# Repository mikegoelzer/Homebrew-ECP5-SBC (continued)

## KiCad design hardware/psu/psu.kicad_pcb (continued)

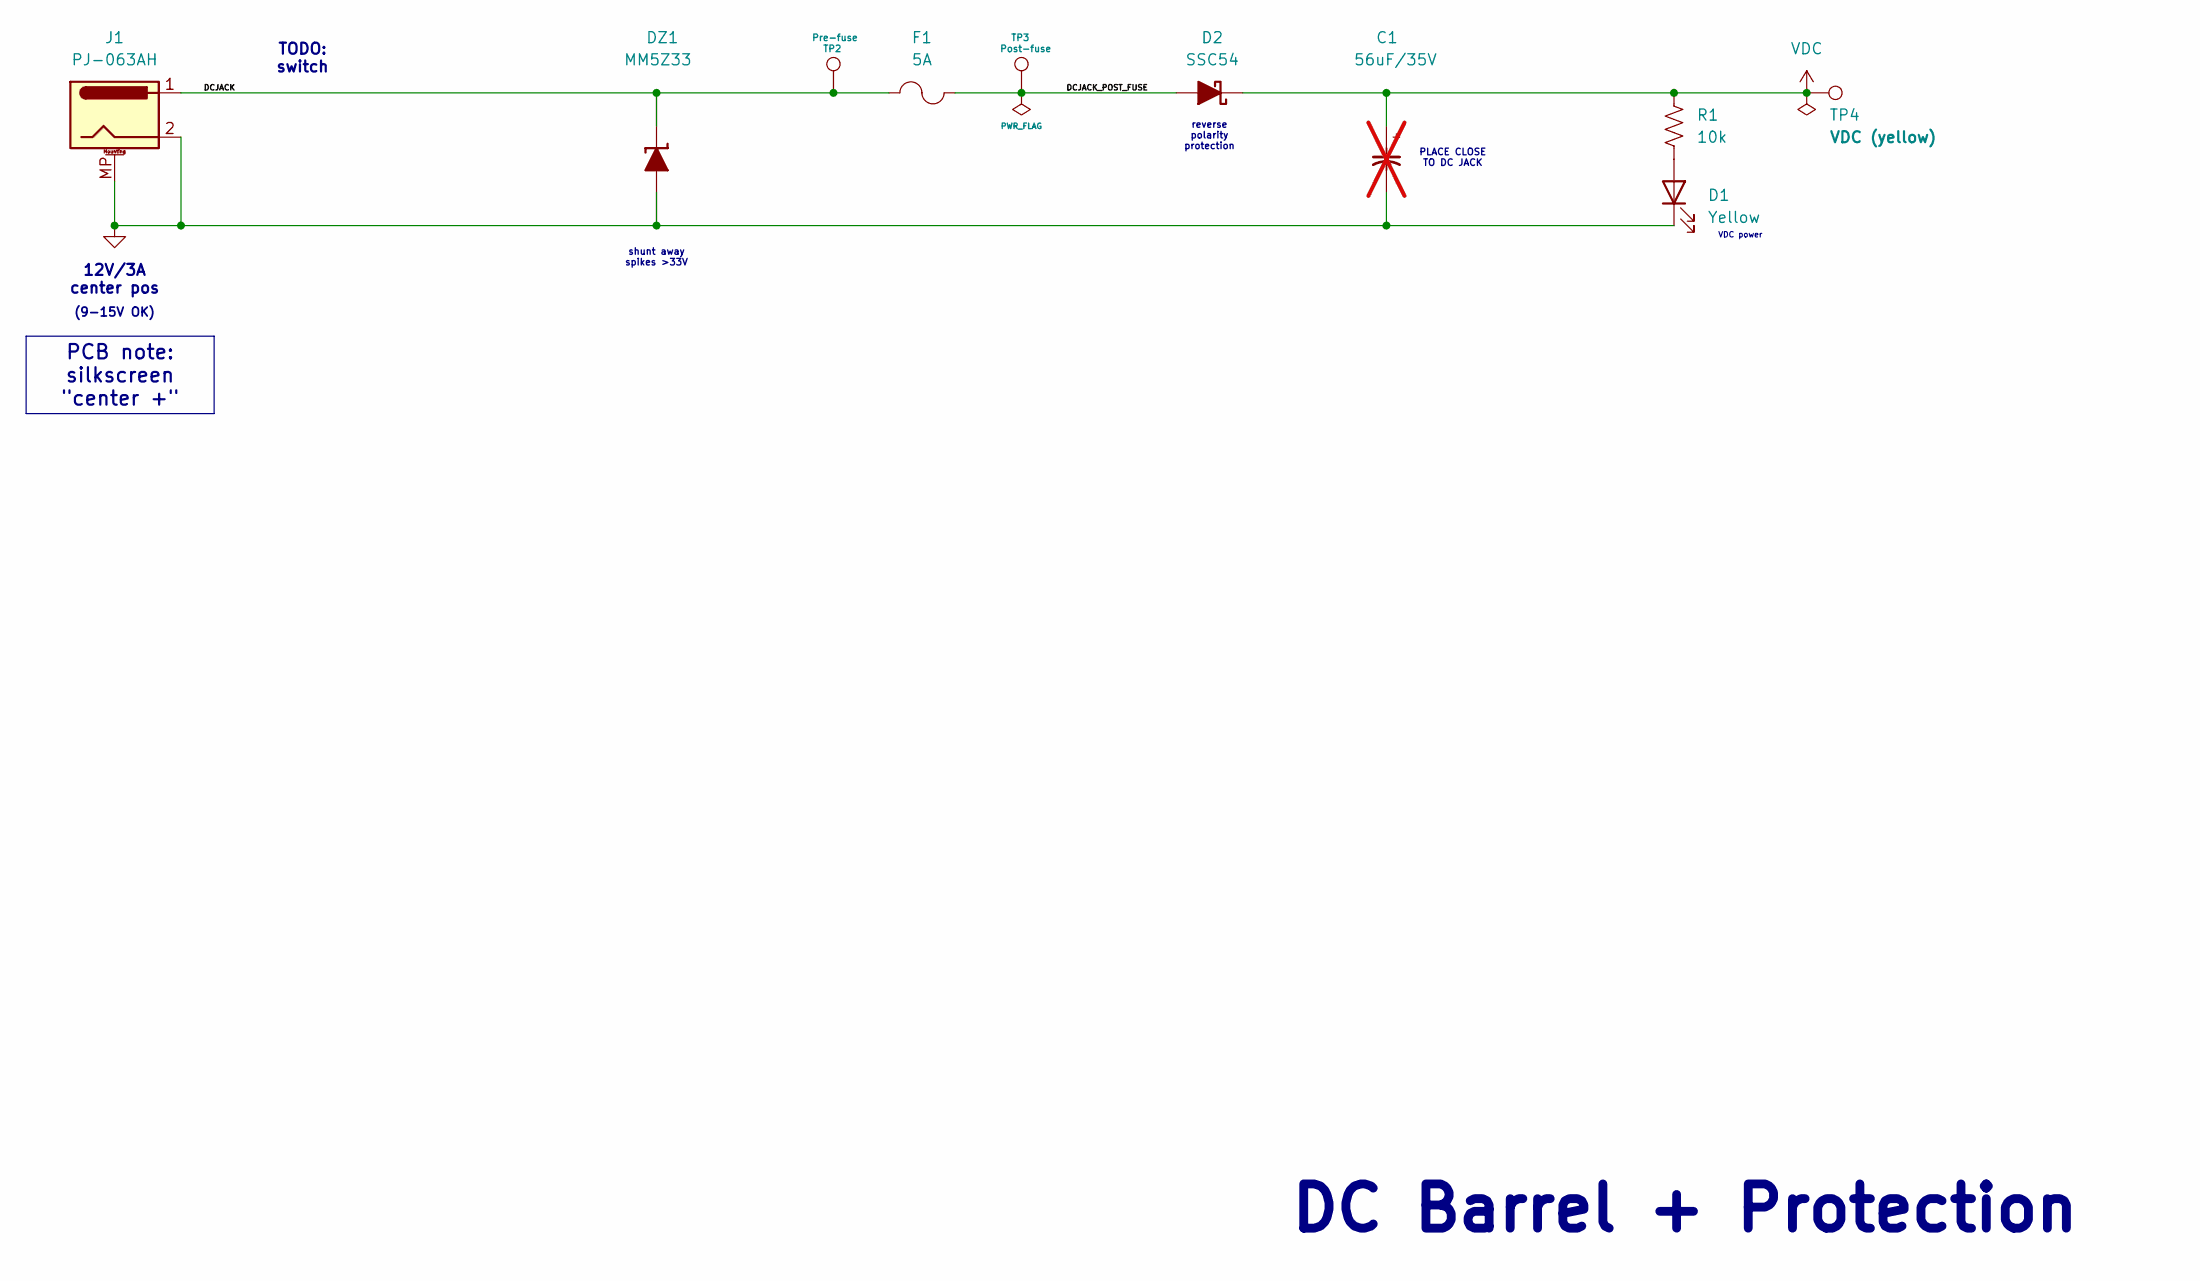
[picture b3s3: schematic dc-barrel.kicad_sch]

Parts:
C1: 56uF/35V; CAP_PC_8X10_NCH; MPN PCV1V560MCL1GS; not fitted
D1: Yellow; LED_0603_1608Metric_Pad1.05x0.95mm_HandSolder; MPN 150060YS75000
D2: SSC54; D_SMC; MPN SSC54-E3/57T
DZ1: MM5Z33; D_SOD-523; MPN MM5Z33VT1G
F1: 5A; Fuseholder_Cylinder-5x20mm_Wuerth_696103101002-SMD_Horizont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; MPN1 696103101002
J1: PJ-063AH; BarrelJack_CUI_PJ-063AH_Horizontal; MPN PJ-063AH
R1: 10k; R_0603_1608Metric_Pad1.05x0.95mm_HandSolder; MPN RC0603FR-0710KL
TP2: Pre-fuse; TestPoint_Pad_2.0x2.0mm
TP3: Post-fuse; TestPoint_Pad_2.0x2.0mm
TP4: VDC (yellow); TestPoint_Keystone_5000-5004_Miniature; MPN 5004

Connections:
/DC Barrel/DCJACK: DZ1.1 (K), F1.1, J1.1, TP2.1
/DC Barrel/DCJACK_POST_FUSE: D2.2 (A), F1.2, TP3.1
GND: C1.2, D1.1 (K), DZ1.2 (A), J1.2, J1.MP (MountPin); also elsewhere on the board
unnamed: D1.2 (A), R1.2
VDC: C1.1, D2.1 (K), R1.1, TP4.1; also elsewhere on the board

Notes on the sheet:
PCB note: silkscreen "center +"
TODO: switch
12V/3A center pos
VDC power
shunt away spikes >33V
DC Barrel + Protection
(9-15V OK)
PLACE CLOSE TO DC JACK
reverse polarity protection

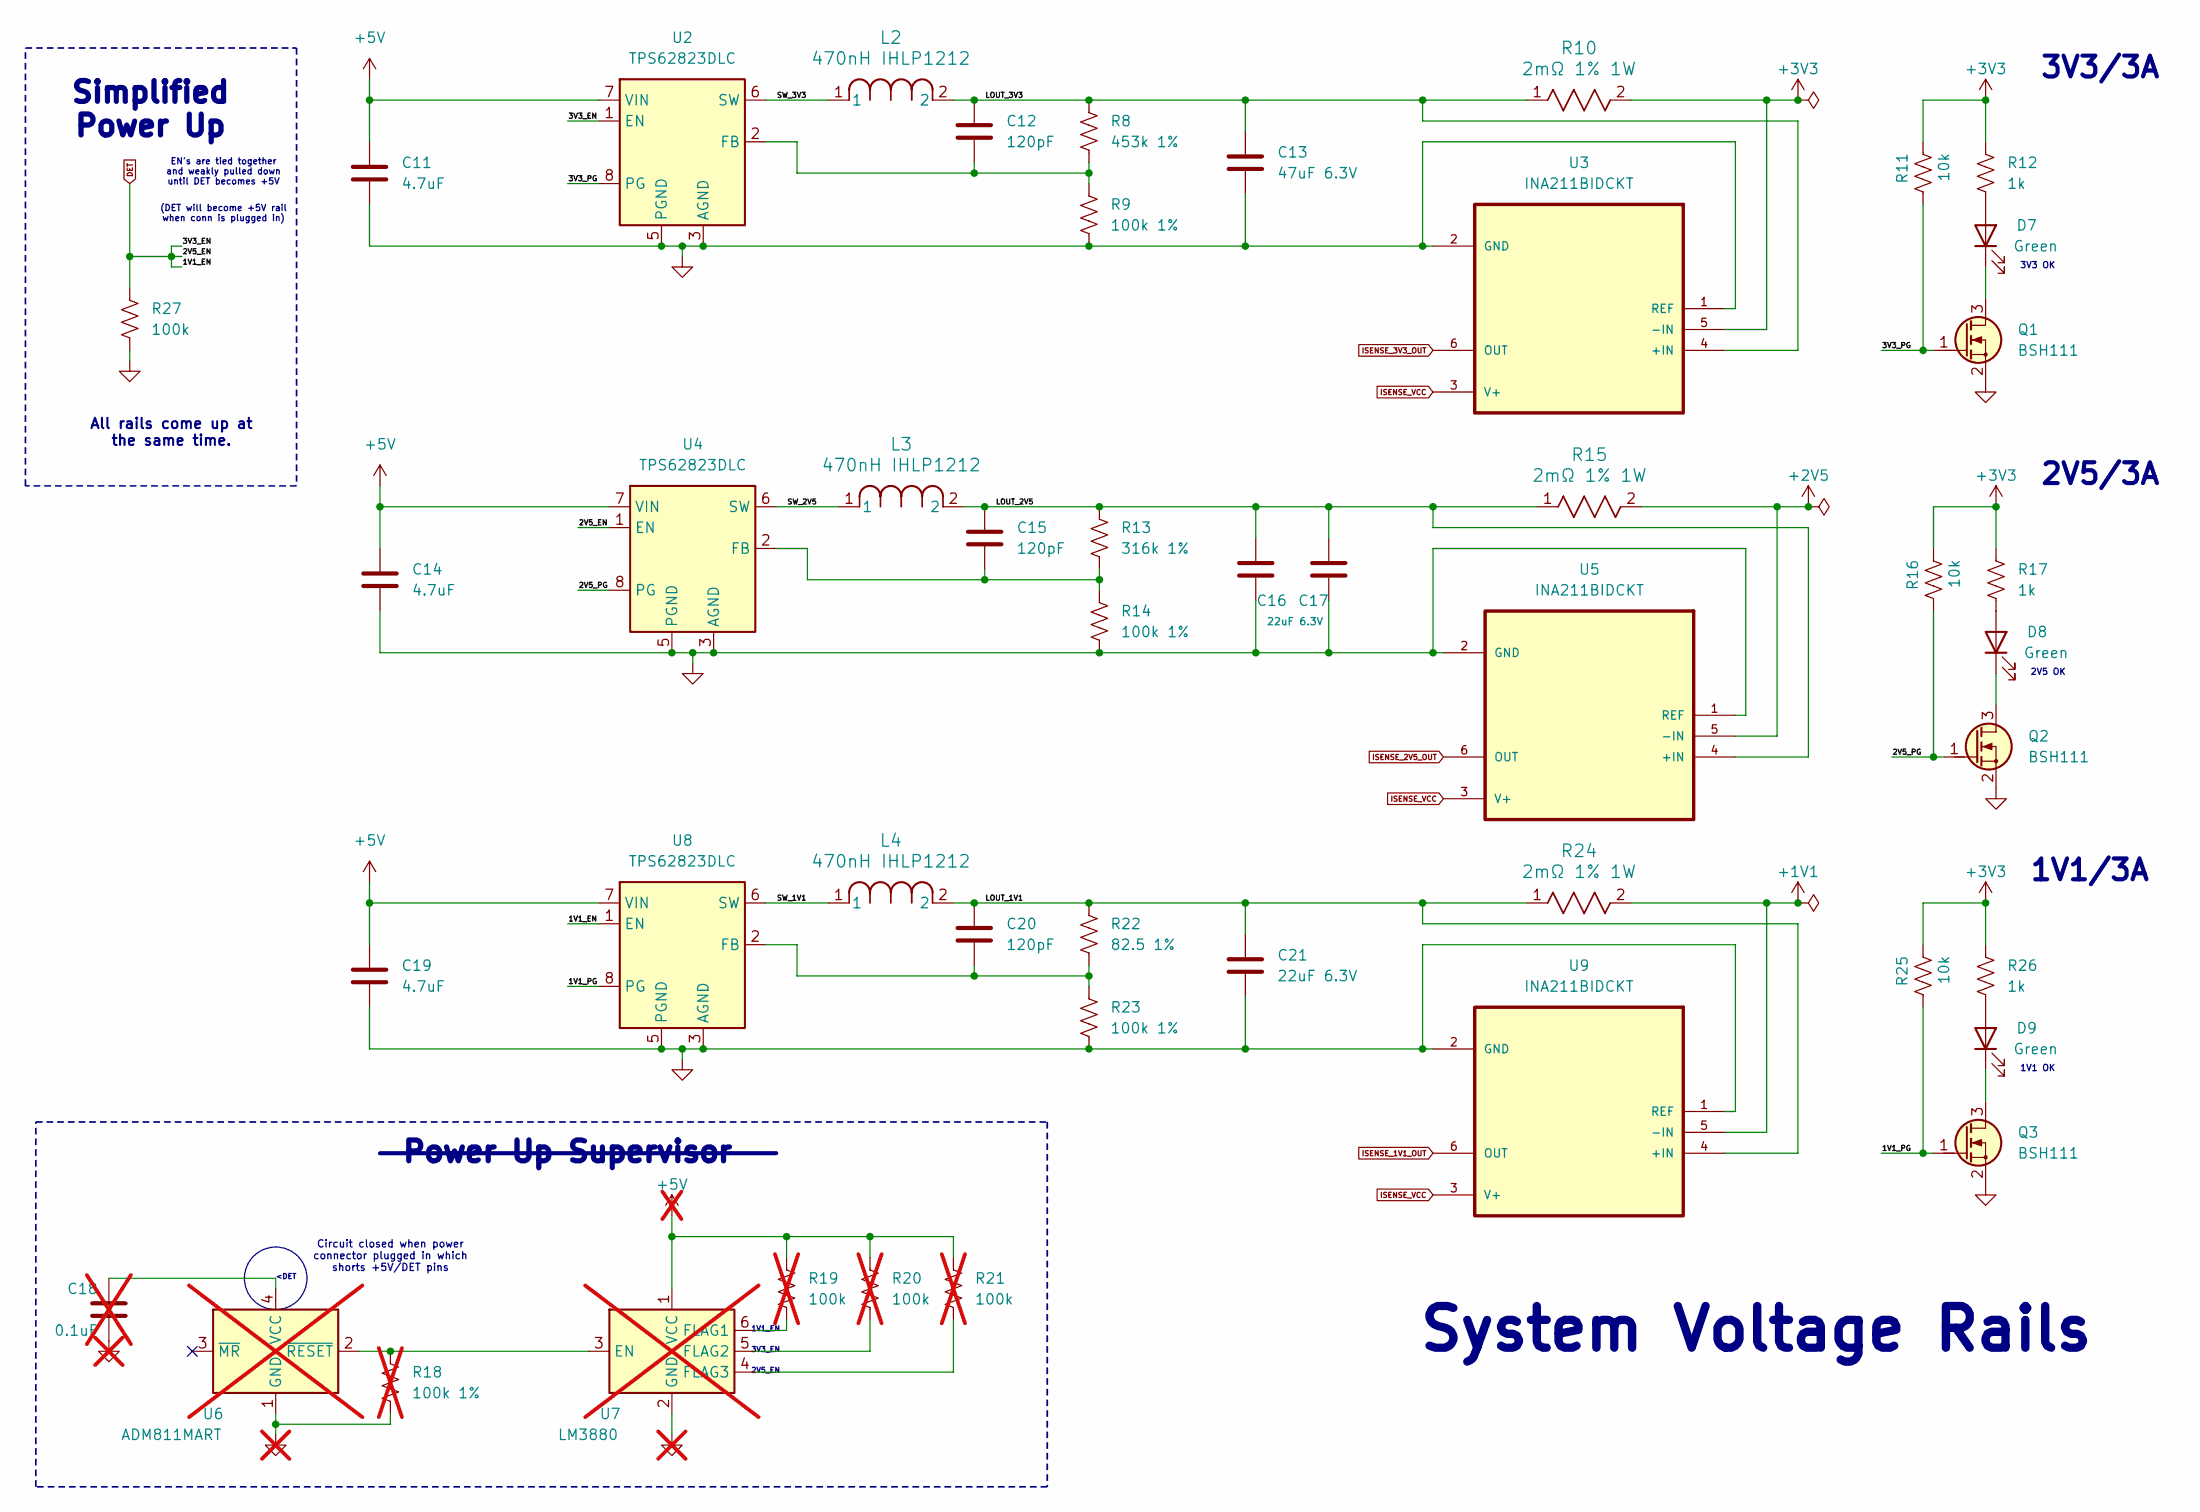
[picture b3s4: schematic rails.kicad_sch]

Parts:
C11, C14, C19: 4.7uF; C_0805_2012Metric_Pad1.18x1.45mm_HandSolder; MPN C0805C475K8PAC7800
C12: 120pF; C_0805_2012Metric_Pad1.18x1.45mm_HandSolder; MPN KGM21BCG1H121JT
C13: 47uF 6.3V; C_1206_3216Metric_Pad1.33x1.80mm_HandSolder; MPN GRM31CR60J476KE19L
C15, C20: 120pF; C_0603_1608Metric_Pad1.08x0.95mm_HandSolder; MPN GRM1885C1H121JA01D
C16, C17, C21: 22uF 6.3V; C_0603_1608Metric_Pad1.08x0.95mm_HandSolder; MPN GRM188R60J226MEA0D
C18: 0.1uF; C_0603_1608Metric_Pad1.08x0.95mm_HandSolder; MPN GRM188R72A104KA35D; not fitted
D7, D8, D9: Green; LED_0603_1608Metric_Pad1.05x0.95mm_HandSolder; MPN 150060VS75000
L2, L3, L4: 470nH IHLP1212; L_Vishay_IHLP-1212; MPN IHLP1212AEERR47M11
Q1, Q2, Q3: BSH111; SOT-23; MPN BSH111BKR
R8: 453k 1%; R_0805_2012Metric_Pad1.15x1.40mm_HandSolder; MPN ERJ-6ENF4533V
R9, R14, R23: 100k 1%; R_0805_2012Metric_Pad1.15x1.40mm_HandSolder; MPN CRCW0805100KFKEA
R10, R15, R24: 2mΩ 1% 1W; STA_CSNL1206_STP; MPN CSNL1206FT2L00
R11, R16, R25: 10k; R_0603_1608Metric_Pad1.05x0.95mm_HandSolder; MPN RC0603FR-0710KL
R12, R17, R26: 1k; R_0603_1608Metric_Pad1.05x0.95mm_HandSolder; MPN RC0603FR-071KL
R13: 316k 1%; R_0805_2012Metric_Pad1.15x1.40mm_HandSolder; MPN ERJ-6ENF3163V
R18: 100k 1%; R_0603_1608Metric_Pad0.98x0.95mm_HandSolder; MPN RC0603FR-07100KL; not fitted
R19, R20, R21: 100k; R_0603_1608Metric_Pad0.98x0.95mm_HandSolder; MPN RC0603FR-07100KL; not fitted
R22: 82.5 1%; R_0805_2012Metric_Pad1.15x1.40mm_HandSolder; MPN ERJ-6ENF8252V
R27: 100k; R_0603_1608Metric_Pad0.98x0.95mm_HandSolder; MPN RC0603FR-07100KL
U2, U4, U8: TPS62823DLC; Texas_VSON-HR-8_1.5x2mm_P0.5mm; MPN TPS62823DLCR
U3, U5, U9: INA211BIDCKT; SOT65P210X110-6N; MPN INA211BIDCKT
U6: ADM811MART; SOT-143; MPN ADM811MARTZ-REEL7; not fitted
U7: LM3880; SOT-23-6; not fitted

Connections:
+1V1: R24.2, U9.5 (-IN); also elsewhere on the board
+2V5: R15.2, U5.5 (-IN); also elsewhere on the board
+3V3: R10.2, R11.2, R12.2, R16.2, R17.2, R25.2, R26.2, U3.5 (-IN); also elsewhere on the board
+5V: C11.1, C14.1, C19.1, R19.1, R20.1, R21.1, U2.7 (VIN), U4.7 (VIN), U7.1 (VCC), U8.7 (VIN); also elsewhere on the board
/Rails/1V1_PG: Q3.1 (G), R25.1, U8.8 (PG)
/Rails/2V5_PG: Q2.1 (G), R16.1, U4.8 (PG)
/Rails/3V3_PG: Q1.1 (G), R11.1, U2.8 (PG)
/Rails/LOUT_1V1: C20.1, C21.1, L4.2, R22.1, R24.1, U9.4 (+IN)
/Rails/LOUT_2V5: C15.1, C16.1, C17.1, L3.2, R13.1, R15.1, U5.4 (+IN)
/Rails/LOUT_3V3: C12.1, C13.1, L2.2, R8.1, R10.1, U3.4 (+IN)
/Rails/SW_1V1: L4.1, U8.6 (SW)
/Rails/SW_2V5: L3.1, U4.6 (SW)
/Rails/SW_3V3: L2.1, U2.6 (SW)
DET: R27.1, U2.1 (EN), U4.1 (EN), U8.1 (EN); also elsewhere on the board
GND: C11.2, C13.2, C14.2, C16.2, C17.2, C18.2, C19.2, C21.2, Q1.2 (S), Q2.2 (S), Q3.2 (S), R9.2, R14.2, R18.2, R23.2, R27.2, U2.3 (AGND), U2.5 (PGND), U3.1 (REF), U3.2 (GND), U4.3 (AGND), U4.5 (PGND), U5.1 (REF), U5.2 (GND), U6.1 (GND), U7.2 (GND), U8.3 (AGND), U8.5 (PGND), U9.1 (REF), U9.2 (GND); also elsewhere on the board
ISENSE_1V1_OUT: U9.6 (OUT); also elsewhere on the board
ISENSE_2V5_OUT: U5.6 (OUT); also elsewhere on the board
ISENSE_3V3_OUT: U3.6 (OUT); also elsewhere on the board
ISENSE_VCC: U3.3 (V+), U5.3 (V+), U9.3 (V+); also elsewhere on the board
unnamed: C18.1, U6.4 (VCC)
unnamed: D7.2 (A), R12.1
unnamed: D7.1 (K), Q1.3 (D)
unnamed: D8.2 (A), R17.1
unnamed: D8.1 (K), Q2.3 (D)
unnamed: D9.2 (A), R26.1
unnamed: D9.1 (K), Q3.3 (D)
unnamed: R18.1, U6.2 (~RESET), U7.3 (EN)
unnamed: R19.2, U7.6 (FLAG1)
unnamed: R20.2, U7.5 (FLAG2)
unnamed: R21.2, U7.4 (FLAG3)
unnamed: C12.2, R8.2, R9.1, U2.2 (FB)
unnamed: C15.2, R13.2, R14.1, U4.2 (FB)
unnamed: C20.2, R22.2, R23.1, U8.2 (FB)

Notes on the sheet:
2V5/3A
Simplified Power Up
3V3_EN
3V3 OK
(DET will become +5V rail when conn is plugged in)
3V3/3A
<DET
System Voltage Rails
1V1_EN
2V5_EN
All rails come up at the same time.
Power Up Supervisor
Circuit closed when power connector plugged in which shorts +5V/DET pins
2V5 OK
EN's are tied together and weakly pulled down until DET becomes +5V
1V1 OK
1V1/3A

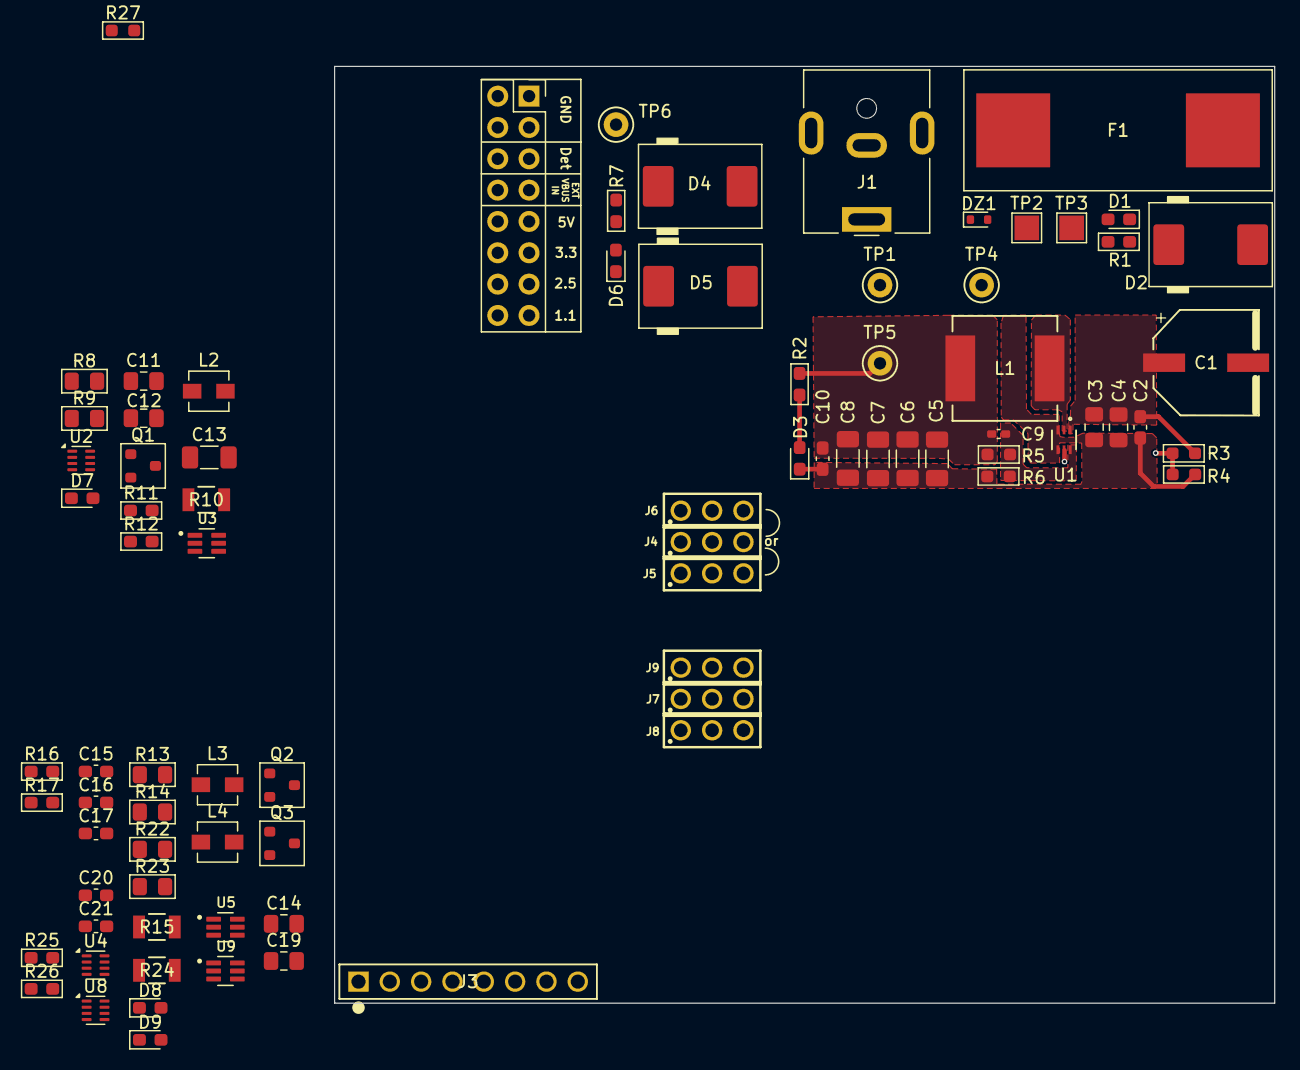
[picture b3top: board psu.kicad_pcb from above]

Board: 4 copper layers, 76.2 x 75.9 mm, 83 parts (0 on the bottom side), 41 nets.

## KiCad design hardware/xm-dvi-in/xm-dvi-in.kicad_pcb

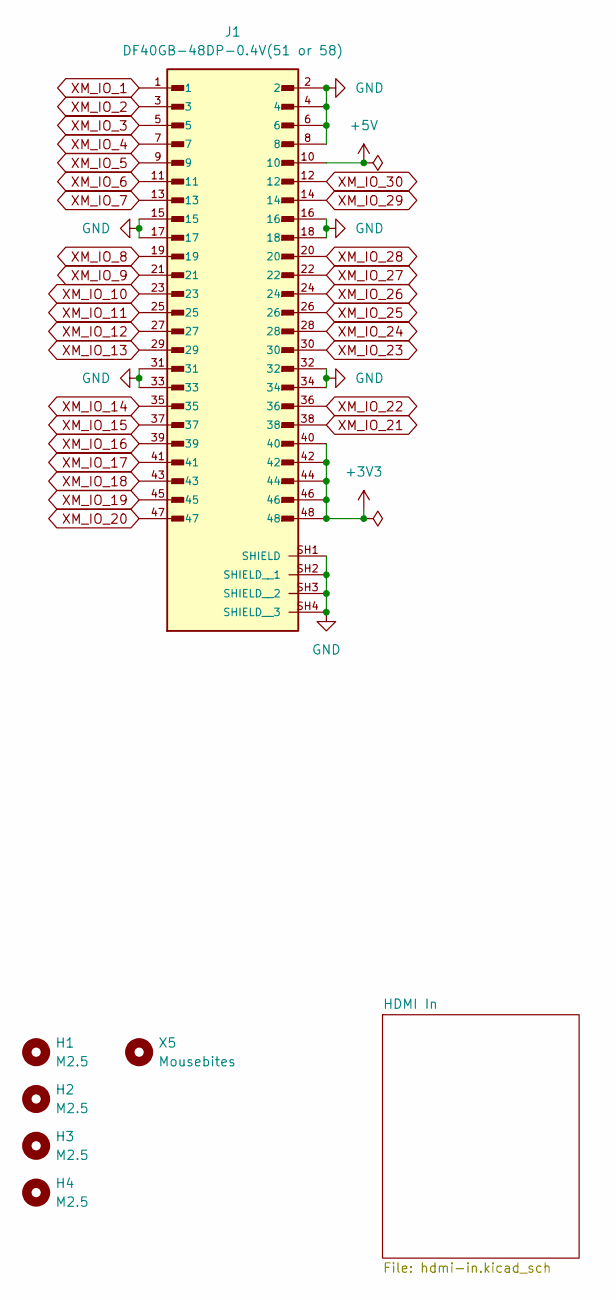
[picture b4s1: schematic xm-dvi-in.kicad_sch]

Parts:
H1, H2, H3, H4: M2.5; MountingHole_2.7mm_M2.5
J1: DF40GB-48DP-0.4V(51 or 58); HIROSE_DF40GB-48DP-0.4V_58_; MPN DF40GB-48DP-0.4V(51)
X5: Mousebites; mouse-bite-2.54mm-slot

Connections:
+3V3: J1.40, J1.42, J1.44, J1.46, J1.48; also elsewhere on the board
+5V: J1.10; also elsewhere on the board
GND: J1.2, J1.4, J1.6, J1.8, J1.15, J1.16, J1.17, J1.18, J1.31, J1.32, J1.33, J1.34, J1.SH1 (SHIELD), J1.SH2 (SHIELD__1), J1.SH3 (SHIELD__2), J1.SH4 (SHIELD__3); also elsewhere on the board
XM_IO_1: J1.1
XM_IO_2: J1.3
XM_IO_3: J1.5
XM_IO_4: J1.7
XM_IO_5: J1.9
XM_IO_6: J1.11
XM_IO_7: J1.13
XM_IO_8: J1.19
XM_IO_9: J1.21
XM_IO_10: J1.23
XM_IO_11: J1.25
XM_IO_12: J1.27
XM_IO_13: J1.29
XM_IO_14: J1.35
XM_IO_15: J1.37
XM_IO_16: J1.39
XM_IO_17: J1.41
XM_IO_18: J1.43
XM_IO_19: J1.45
XM_IO_20: J1.47
XM_IO_21: J1.38
XM_IO_22: J1.36
XM_IO_23: J1.30
XM_IO_24: J1.28
XM_IO_25: J1.26
XM_IO_26: J1.24
XM_IO_27: J1.22
XM_IO_28: J1.20
XM_IO_29: J1.14
XM_IO_30: J1.12

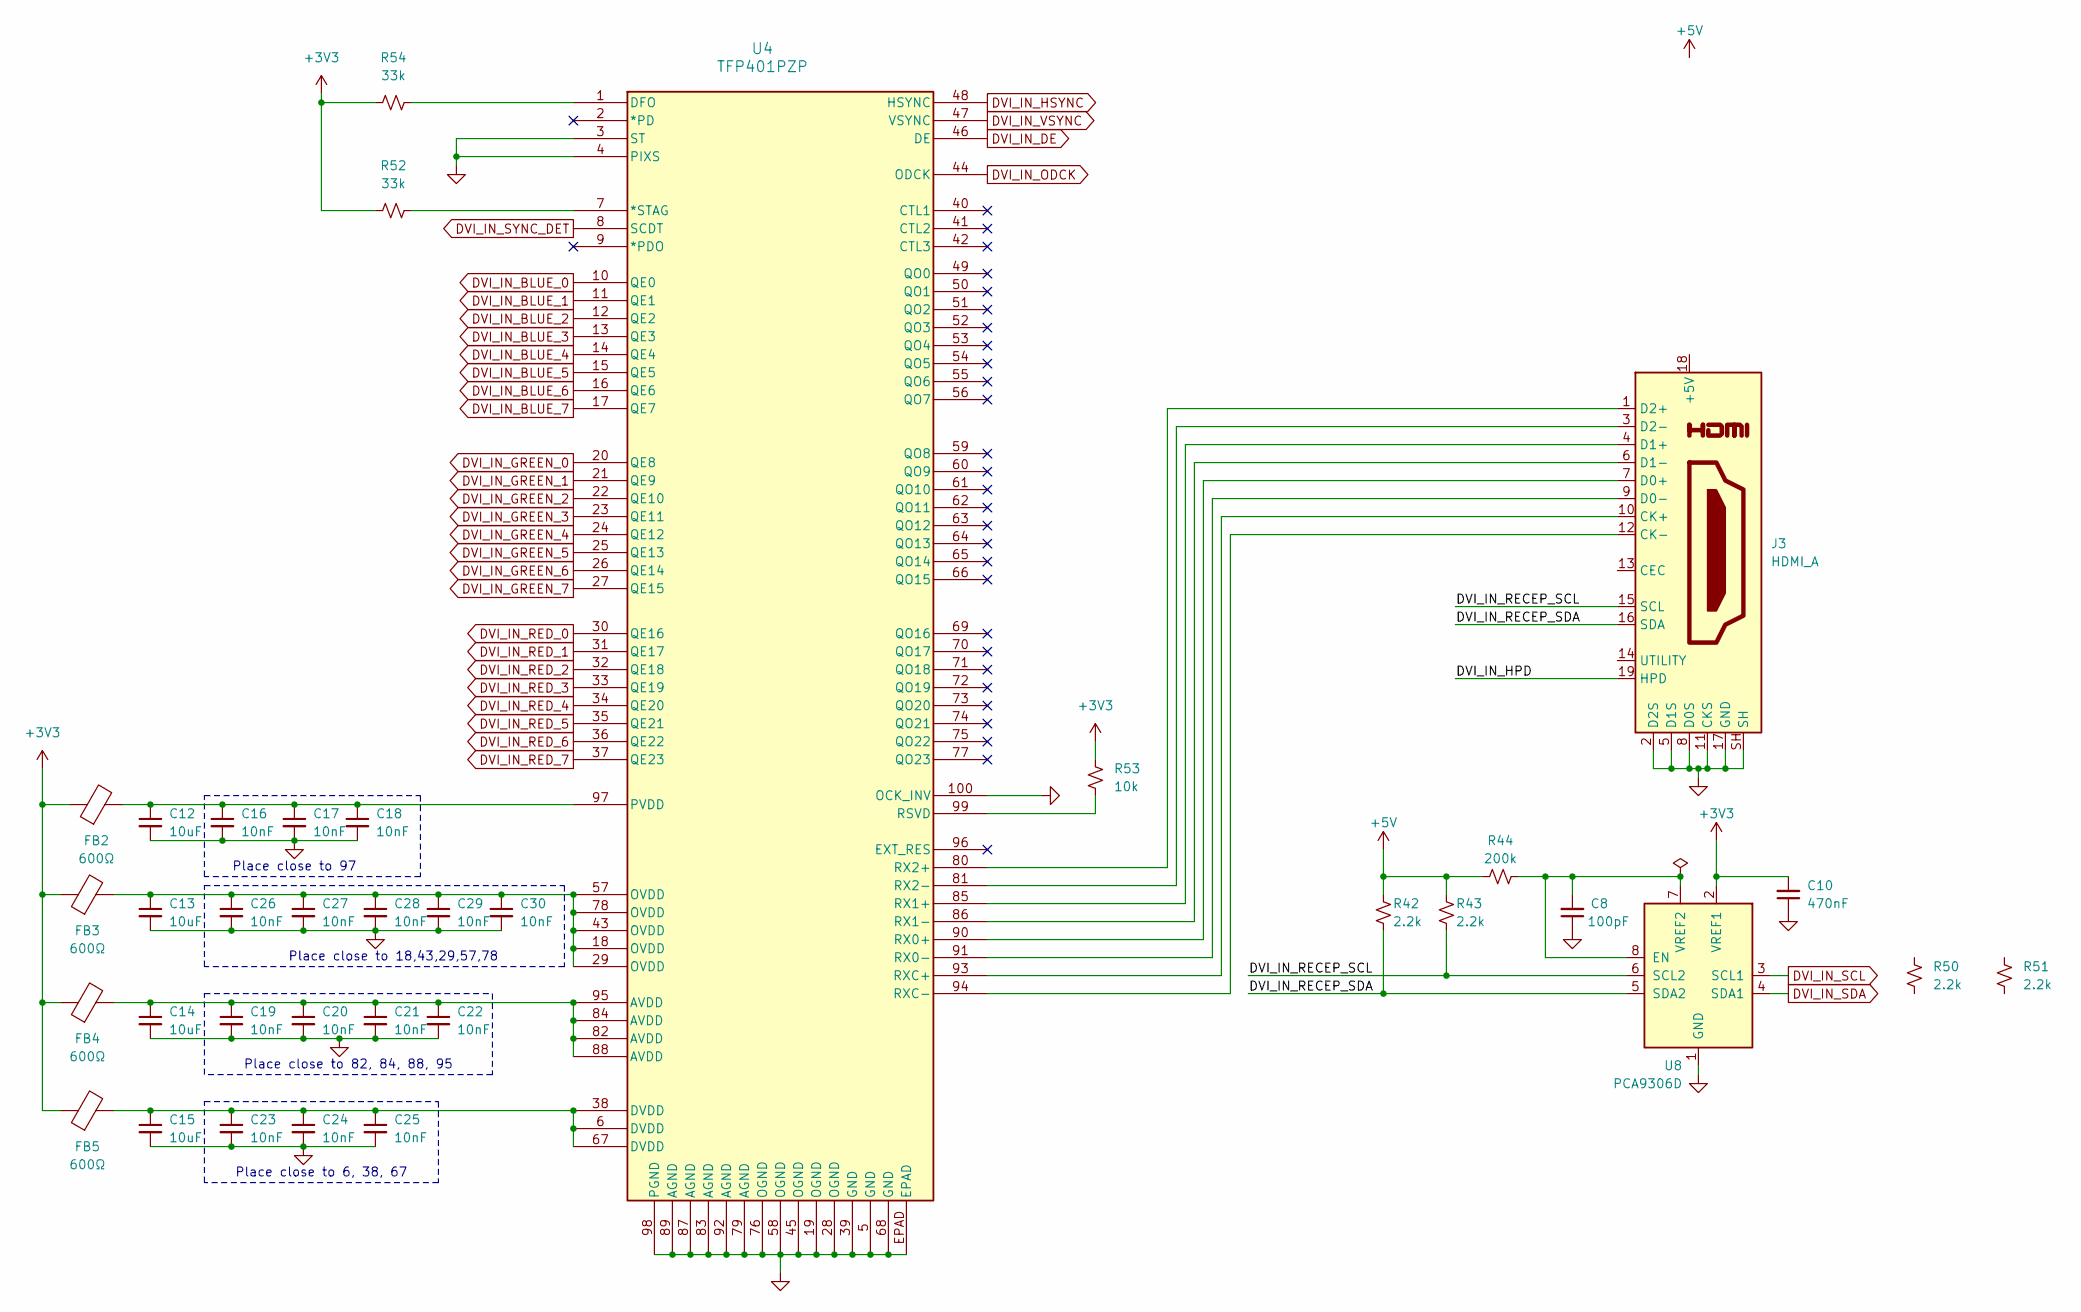
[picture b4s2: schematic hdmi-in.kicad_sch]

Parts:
C8: 100pF; C_0805_2012Metric_Pad1.18x1.45mm_HandSolder; MPN CC0805KRX7R9BB101
C10: 470nF; C_0805_2012Metric_Pad1.18x1.45mm_HandSolder; MPN CC0805KKX7R8BB474
C12, C13, C14, C15: 10uF; C_0805_2012Metric_Pad1.18x1.45mm_HandSolder; MPN CC0805KKX5R8BB106
C16, C17, C18, C19, C20, C21, C22, C23, C24, C25, C26, C27, C28, C29, C30: 10nF; C_0805_2012Metric_Pad1.18x1.45mm_HandSolder; MPN CC0805KRX7R9BB103
FB2, FB3, FB4, FB5: 600Ω; L_0603_1608Metric_Pad1.05x0.95mm_HandSolder; MPN BLM18RK601SN1D
J3: HDMI_A; HDMI_A_Molex_208658-1001_Horizontal; MPN 2086581001
R42, R43, R50, R51: 2.2k; R_0805_2012Metric_Pad1.15x1.40mm_HandSolder; MPN RC0805FR-072K2L
R44: 200k; R_0805_2012Metric_Pad1.15x1.40mm_HandSolder; MPN RC0805FR-07200KL
R52, R54: 33k; R_0805_2012Metric_Pad1.15x1.40mm; MPN RC0805FR-0733KL
R53: 10k; R_0805_2012Metric_Pad1.15x1.40mm; MPN RC0805FR-0710KL
U4: TFP401PZP; PZP100_5P2X5P2; MPN TFP401PZP
U8: PCA9306D; SO-8_3.9x4.9mm_P1.27mm; MPN PCA9306D,118

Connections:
+3V3: C10.2, FB2.1, FB3.1, FB4.1, FB5.1, R52.2, R53.2, R54.1, U8.2 (VREF1); also elsewhere on the board
+5V: R42.1, R43.1, R44.1; also elsewhere on the board
/HDMI In/DVI_IN_HPD: J3.19 (HPD)
/HDMI In/DVI_IN_RECEP_SCL: J3.15 (SCL), R43.2, U8.6 (SCL2)
/HDMI In/DVI_IN_RECEP_SDA: J3.16 (SDA), R42.2, U8.5 (SDA2)
DVI_IN_BLUE_0: U4.10 (QE0)
DVI_IN_BLUE_1: U4.11 (QE1)
DVI_IN_BLUE_2: U4.12 (QE2)
DVI_IN_BLUE_3: U4.13 (QE3)
DVI_IN_BLUE_4: U4.14 (QE4)
DVI_IN_BLUE_5: U4.15 (QE5)
DVI_IN_BLUE_6: U4.16 (QE6)
DVI_IN_BLUE_7: U4.17 (QE7)
DVI_IN_DE: U4.46 (DE)
DVI_IN_GREEN_0: U4.20 (QE8)
DVI_IN_GREEN_1: U4.21 (QE9)
DVI_IN_GREEN_2: U4.22 (QE10)
DVI_IN_GREEN_3: U4.23 (QE11)
DVI_IN_GREEN_4: U4.24 (QE12)
DVI_IN_GREEN_5: U4.25 (QE13)
DVI_IN_GREEN_6: U4.26 (QE14)
DVI_IN_GREEN_7: U4.27 (QE15)
DVI_IN_HSYNC: U4.48 (HSYNC)
DVI_IN_ODCK: U4.44 (ODCK)
DVI_IN_RED_0: U4.30 (QE16)
DVI_IN_RED_1: U4.31 (QE17)
DVI_IN_RED_2: U4.32 (QE18)
DVI_IN_RED_3: U4.33 (QE19)
DVI_IN_RED_4: U4.34 (QE20)
DVI_IN_RED_5: U4.35 (QE21)
DVI_IN_RED_6: U4.36 (QE22)
DVI_IN_RED_7: U4.37 (QE23)
DVI_IN_SCL: U8.3 (SCL1)
DVI_IN_SDA: U8.4 (SDA1)
DVI_IN_SYNC_DET: U4.8 (SCDT)
DVI_IN_VSYNC: U4.47 (VSYNC)
GND: C8.1, C10.1, C12.2, C13.2, C14.2, C15.2, C16.2, C17.2, C18.2, C19.2, C20.2, C21.2, C22.2, C23.2, C24.2, C25.2, C26.2, C27.2, C28.2, C29.2, C30.2, J3.2 (D2S), J3.5 (D1S), J3.8 (D0S), J3.11 (CKS), J3.17 (GND), J3.SH, U4.3 (ST), U4.4 (PIXS), U4.5 (GND), U4.19 (OGND), U4.28 (OGND), U4.39 (GND), U4.45 (OGND), U4.58 (OGND), U4.68 (GND), U4.76 (OGND), U4.79 (AGND), U4.83 (AGND), U4.87 (AGND), U4.89 (AGND), U4.92 (AGND), U4.98 (PGND), U4.100 (OCK_INV), U4.EPAD, U8.1 (GND); also elsewhere on the board
unnamed: C13.1, C26.1, C27.1, C28.1, C29.1, C30.1, FB3.2, U4.18 (OVDD), U4.29 (OVDD), U4.43 (OVDD), U4.57 (OVDD), U4.78 (OVDD)
unnamed: C14.1, C19.1, C20.1, C21.1, C22.1, FB4.2, U4.82 (AVDD), U4.84 (AVDD), U4.88 (AVDD), U4.95 (AVDD)
unnamed: C15.1, C23.1, C24.1, C25.1, FB5.2, U4.6 (DVDD), U4.38 (DVDD), U4.67 (DVDD)
unnamed: J3.10 (CK+), U4.93 (RXC+)
unnamed: J3.12 (CK-), U4.94 (RXC-)
unnamed: J3.7 (D0+), U4.90 (RX0+)
unnamed: J3.9 (D0-), U4.91 (RX0-)
unnamed: J3.4 (D1+), U4.85 (RX1+)
unnamed: J3.6 (D1-), U4.86 (RX1-)
unnamed: J3.1 (D2+), U4.80 (RX2+)
unnamed: J3.3 (D2-), U4.81 (RX2-)
unnamed: R52.1, U4.7 (*STAG)
unnamed: R54.2, U4.1 (DFO)
unnamed: C12.1, C16.1, C17.1, C18.1, FB2.2, U4.97 (PVDD)
unnamed: R53.1, U4.99 (RSVD)
unnamed: C8.2, R44.2, U8.7 (VREF2), U8.8 (EN)

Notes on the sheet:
Place close to 82, 84, 88, 95
Place close to 18,43,29,57,78
Place close to 6, 38, 67
Place close to 97

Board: 4 copper layers, 42 parts (2 on the bottom side), 21 nets, no tracks yet.
